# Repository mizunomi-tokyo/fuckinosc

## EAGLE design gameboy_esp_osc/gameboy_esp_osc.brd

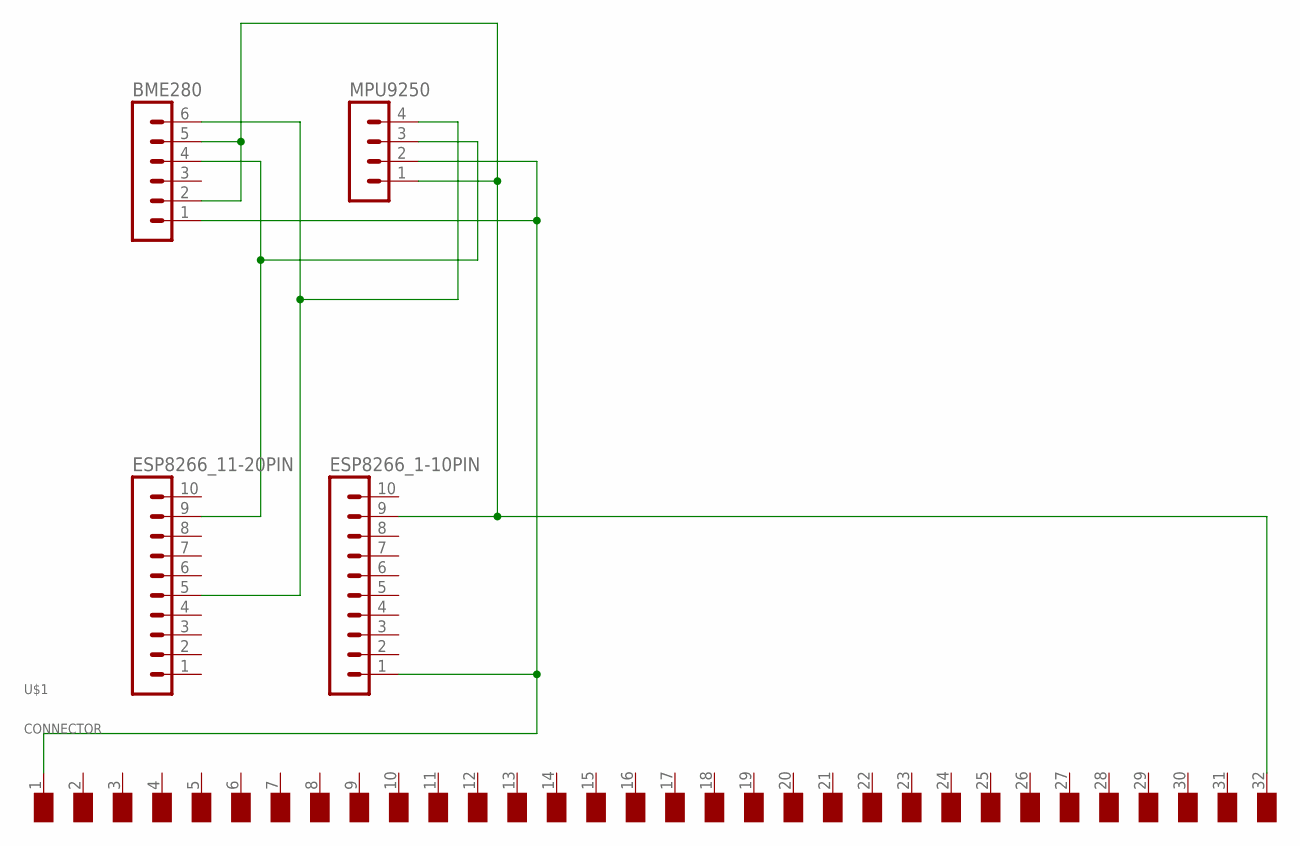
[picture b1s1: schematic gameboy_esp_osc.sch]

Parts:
BME280: MA06-1
ESP8266_1-10PIN, ESP8266_11-20PIN: MA10-1
MPU9250: MA04-1
U$1: CONNECTOR

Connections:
unnamed: BME280.1, ESP8266_1-10PIN.1, MPU9250.2, U$1.1 (VDD)
unnamed: BME280.2, BME280.5, ESP8266_1-10PIN.9, MPU9250.1, U$1.32 (GND)
unnamed: BME280.4, ESP8266_11-20PIN.9, MPU9250.3
unnamed: BME280.6, ESP8266_11-20PIN.5, MPU9250.4

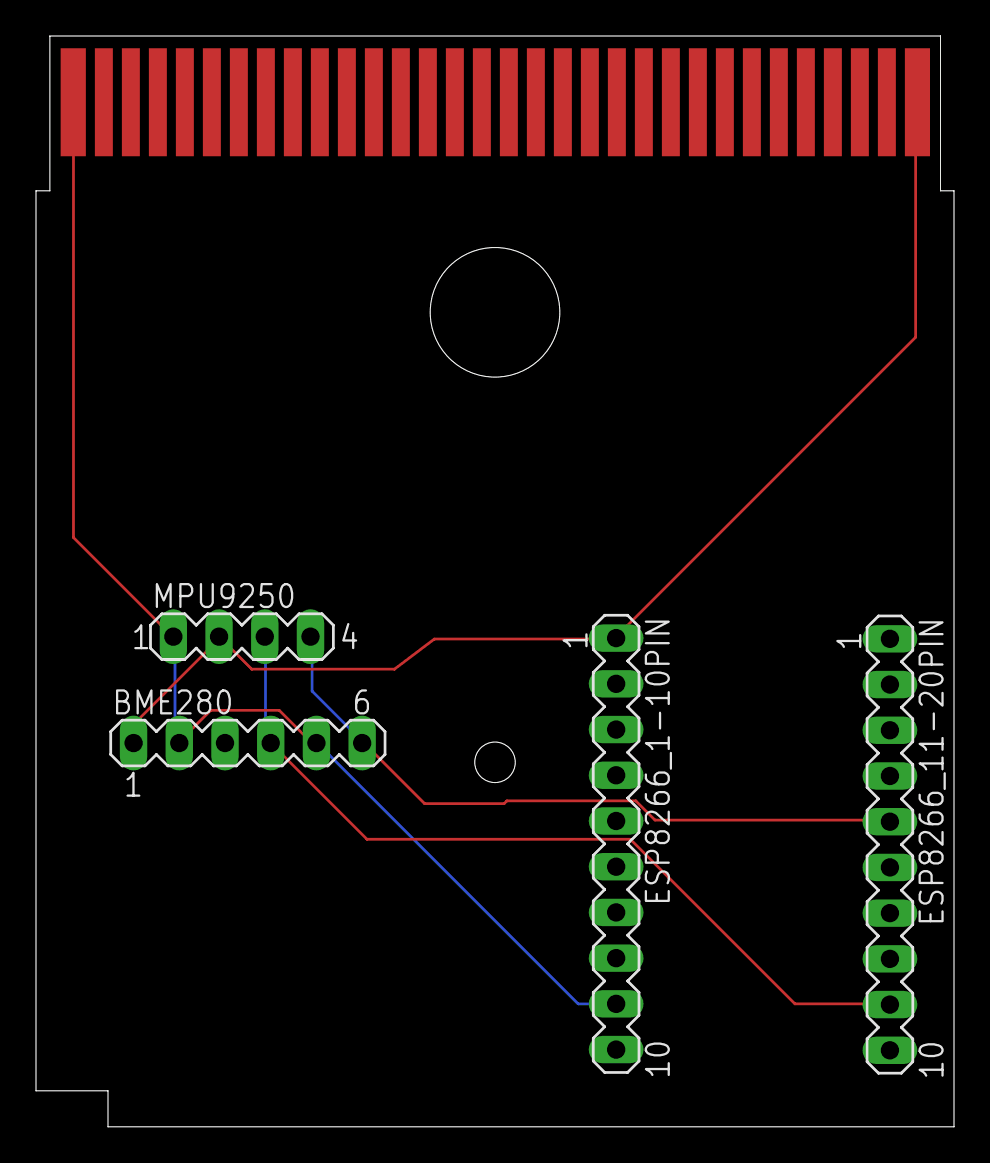
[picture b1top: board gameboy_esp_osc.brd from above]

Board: 2 copper layers, 51.0 x 60.6 mm, 5 parts (0 on the bottom side), 4 nets.

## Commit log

2017-11-20 Create hoge
2017-11-20 Add Arduino codes
2017-11-20 fix ReadMe
2017-11-24 add pcb files
2017-11-24 add silk
2017-12-20 fix osc message
